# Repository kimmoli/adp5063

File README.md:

adp5063
=======

ADP5063 Lipo Charger with LPC81X microcontroller

LPC81X is connected through I2C to the ADP5063

MicroUSB connector to supply 5V in

Almost all pins routed available to headers.

Use as Lipo powered breadboard CPU - Charge via USB.

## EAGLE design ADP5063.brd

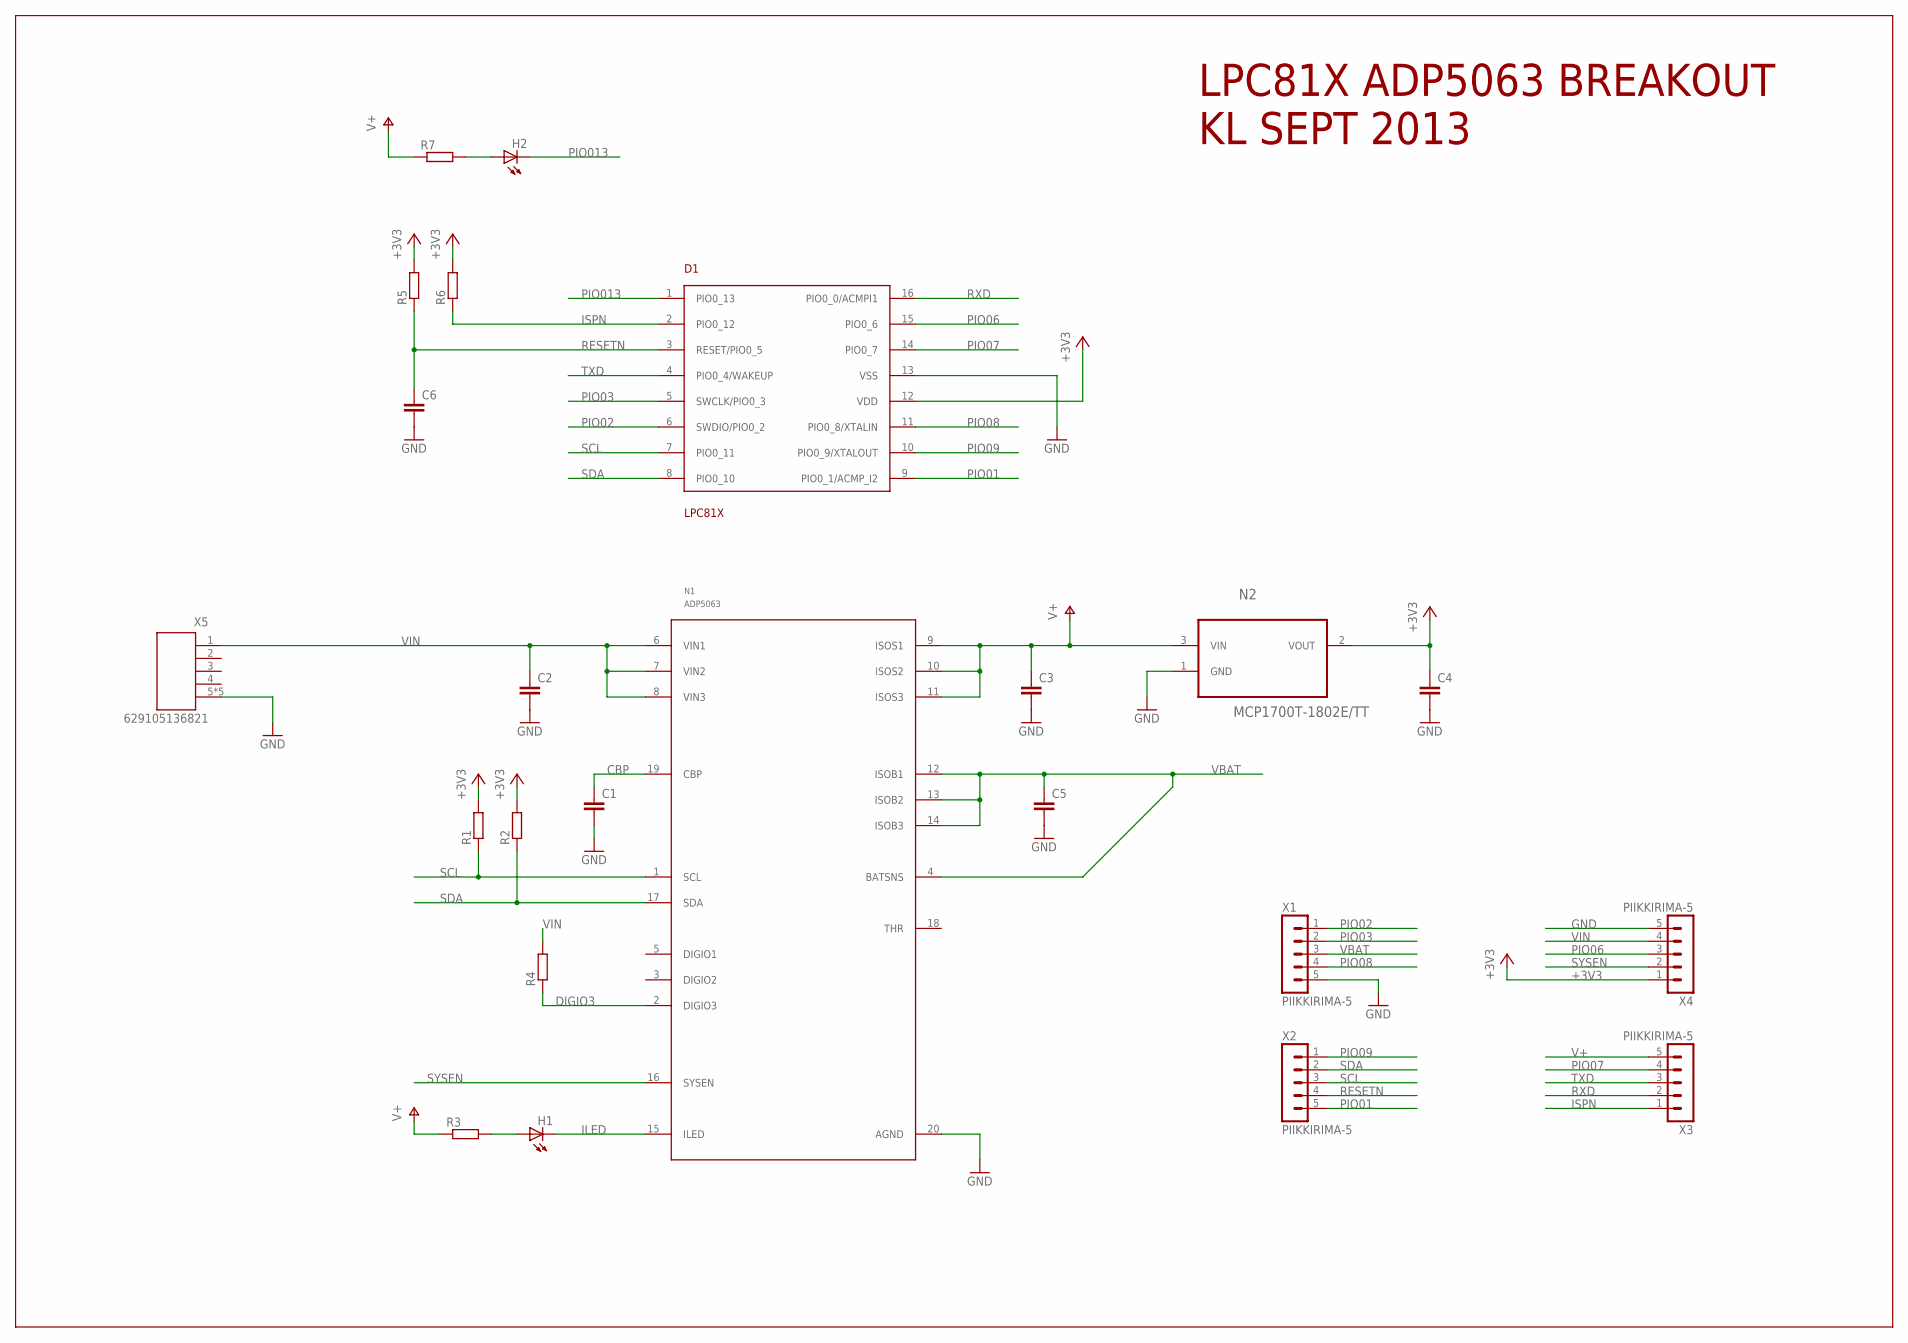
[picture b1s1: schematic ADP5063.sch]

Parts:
C1, C6: C-EUC0603; C0603
C2, C3, C4, C5: C-EUC1206; C1206
D1: LPC81X; TSSOP16
H1, H2: LEDCHIP-LED0603; CHIP-LED0603
N1: ADP5063; QFN50P400X400X80-21N
N2: MCP1700T-1802E/TT; SOT95P237X112-3N
R1, R2, R3, R4, R5, R6, R7: R-EU_R0603; R0603
X1, X2, X3, X4: PIIKKIRIMA-5
X5: 629105136821

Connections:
+3V3: C4.1, D1.12 (VDD), N2.2 (VOUT), R1.2, R2.2, R5.2, R6.2, X4.1
CBP: C1.1, N1.19 (CBP)
DIGIO3: N1.2 (DIGIO3), R4.1
GND: C1.2, C2.2, C3.2, C4.2, C5.2, C6.2, D1.13 (VSS), N1.20 (AGND), N2.1 (GND), X1.5, X4.5, X5.5, X5.Z1 (5), X5.Z2 (5), X5.Z3 (5), X5.Z4 (5)
ILED: H1.C, N1.15 (ILED)
ISPN: D1.2 (PIO0_12), R6.1, X3.1
unnamed: H1.A, R3.2
unnamed: H2.A, R7.2
PIO01: D1.9 (PIO0_1/ACMP_I2), X2.5
PIO02: D1.6 (SWDIO/PIO0_2), X1.1
PIO03: D1.5 (SWCLK/PIO0_3), X1.2
PIO06: D1.15 (PIO0_6), X4.3
PIO07: D1.14 (PIO0_7), X3.4
PIO08: D1.11 (PIO0_8/XTALIN), X1.4
PIO09: D1.10 (PIO0_9/XTALOUT), X2.1
PIO013: D1.1 (PIO0_13), H2.C
RESETN: C6.1, D1.3 (RESET/PIO0_5), R5.1, X2.4
RXD: D1.16 (PIO0_0/ACMPI1), X3.2
SCL: D1.7 (PIO0_11), N1.1 (SCL), R1.1, X2.3
SDA: D1.8 (PIO0_10), N1.17 (SDA), R2.1, X2.2
SYSEN: N1.16 (SYSEN), X4.2
TXD: D1.4 (PIO0_4/WAKEUP), X3.3
V+: C3.1, N1.9 (ISOS1), N1.10 (ISOS2), N1.11 (ISOS3), N2.3 (VIN), R3.1, R7.1, X3.5
VBAT: C5.1, N1.4 (BATSNS), N1.12 (ISOB1), N1.13 (ISOB2), N1.14 (ISOB3), X1.3
VIN: C2.1, N1.6 (VIN1), N1.7 (VIN2), N1.8 (VIN3), R4.2, X4.4, X5.1

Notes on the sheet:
LPC81X ADP5063 BREAKOUT KL SEPT 2013

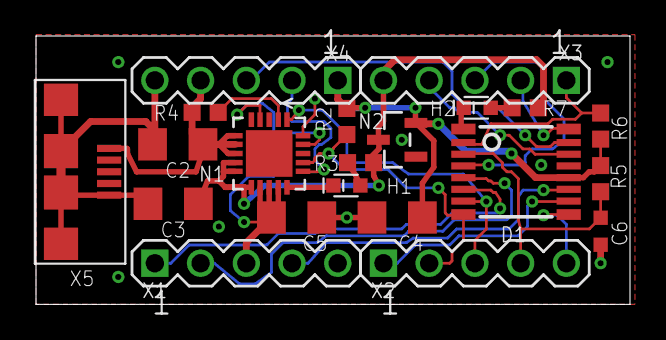
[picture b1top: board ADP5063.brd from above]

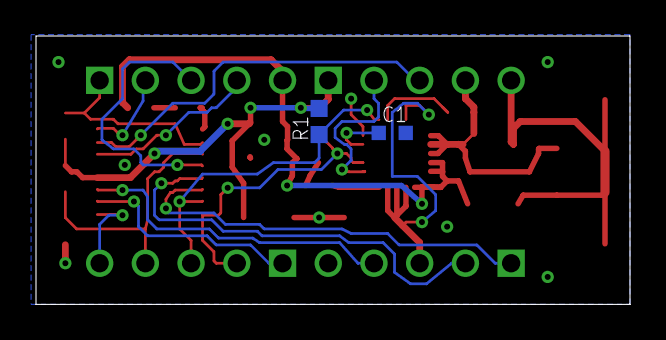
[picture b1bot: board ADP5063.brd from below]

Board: 2 copper layers, 33.0 x 14.9 mm, 24 parts (3 on the bottom side), 25 nets.

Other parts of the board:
U$1: DAFUG-.SM

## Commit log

2013-09-07 Initial commit
    Ordered 3 pcs from OSHpark.com
2013-09-27 VCC/GND Fixed
2013-09-27 Added avatar
